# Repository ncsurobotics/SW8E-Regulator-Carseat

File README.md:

# SW8E-Regulator-Carseat
Holding board for the on-board computer dual regulator setup

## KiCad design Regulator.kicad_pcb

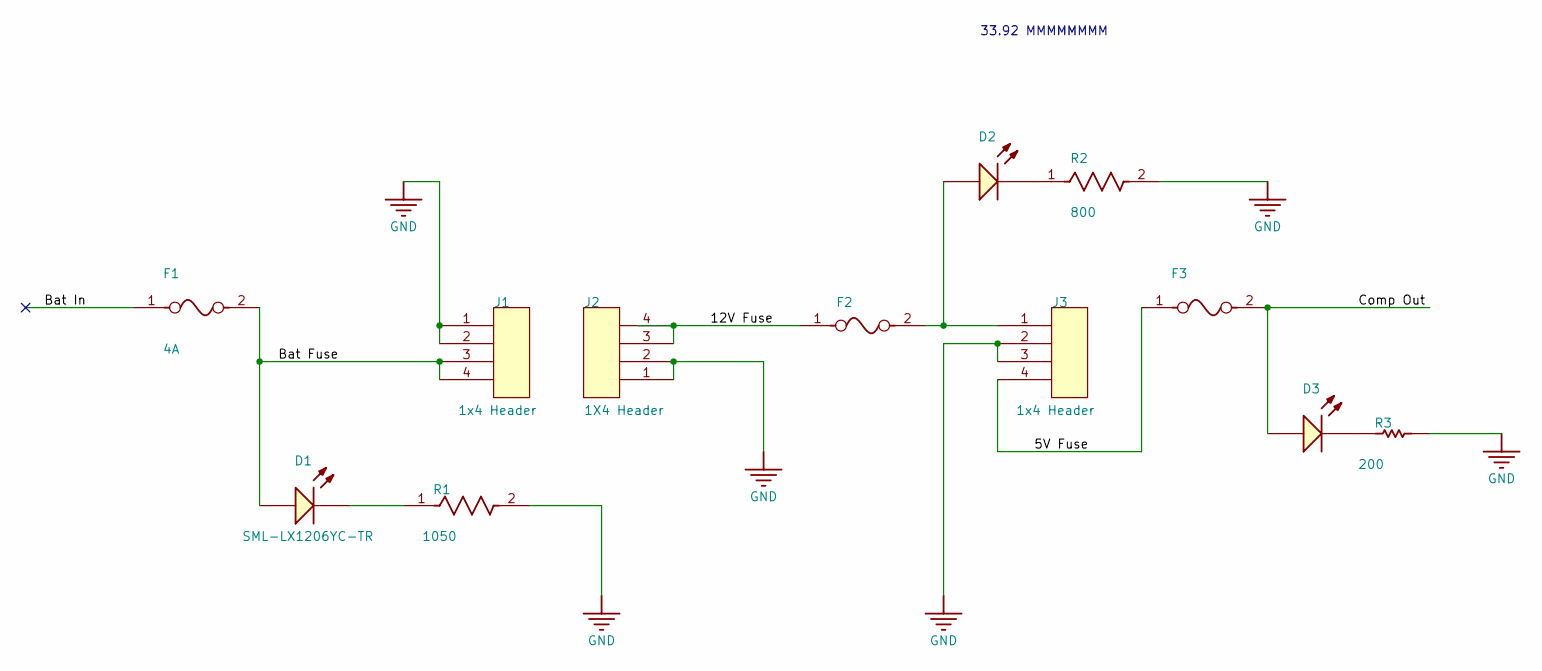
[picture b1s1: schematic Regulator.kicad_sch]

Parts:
D1, D2, D3: SML-LX1206YC-TR; LUMX-SML-LX1206YC-TR_V; Part Number SML-LX1206YC-TR
F1: 4A; FP-0685T-IPC_B; Part Number 0466004.NR
F2: 3A; FP-0466-MFG; Part Number 0466003.NR
F3: 5A; FP-0469-MFG; Part Number 0466005.NR
J1, J3: 1x4 Header; 1X4 HEADER
J2: 1X4 Header; 1X4 HEADER
R1: 1050; R_1206_3216Metric_Pad1.30x1.75mm_HandSolder
R2: 800; R_1206_3216Metric_Pad1.30x1.75mm_HandSolder
R3: 200; R_1206_3216Metric_Pad1.30x1.75mm_HandSolder

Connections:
/5V Fuse: F3.1, J3.4
/12V Fuse: F2.1, J2.3, J2.4
/Bat Fuse: D1.1 (A), F1.2, J1.3, J1.4
/Bat In: F1.1
/Comp Out: D3.1 (A), F3.2
GND: J1.1, J1.2, J2.1, J2.2, J3.2, J3.3, R1.2, R2.2, R3.2
unnamed: D1.2 (K), R1.1
unnamed: D2.1 (A), F2.2, J3.1
unnamed: D2.2 (K), R2.1
unnamed: D3.2 (K), R3.1

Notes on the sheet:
33.92 MMMMMMMM

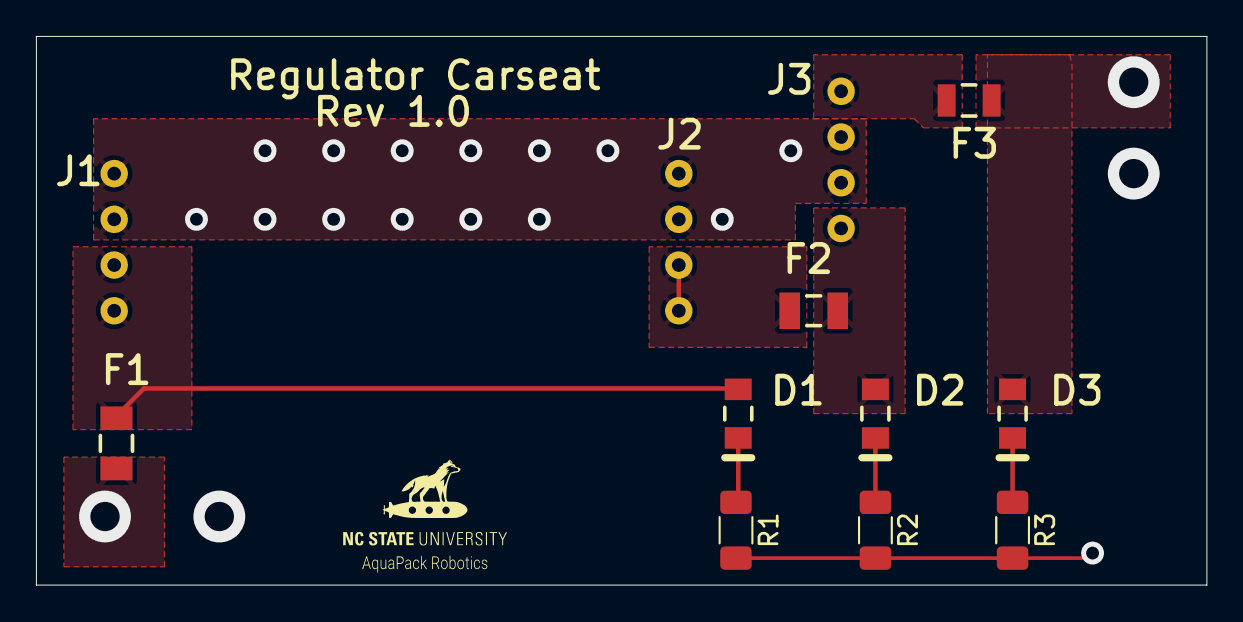
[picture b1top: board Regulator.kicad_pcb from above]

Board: 2 copper layers, 65.0 x 30.5 mm, 12 parts (0 on the bottom side), 9 nets.

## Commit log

2023-02-14 Initial commits, migrated files from local directory
2023-02-14 Added silkscreen for board name and version number
2023-03-23 Added mounting holes and logos
2023-04-11 Imported Regulator to Kicad
2023-07-04 Cleanup files and component linkage errors
2023-07-04 Fix silkscreen logos
2023-07-04 Cleanup component properties and footprints table
2023-07-04 Remove imported symbol table fiends
2023-07-04 Update board settings from template
